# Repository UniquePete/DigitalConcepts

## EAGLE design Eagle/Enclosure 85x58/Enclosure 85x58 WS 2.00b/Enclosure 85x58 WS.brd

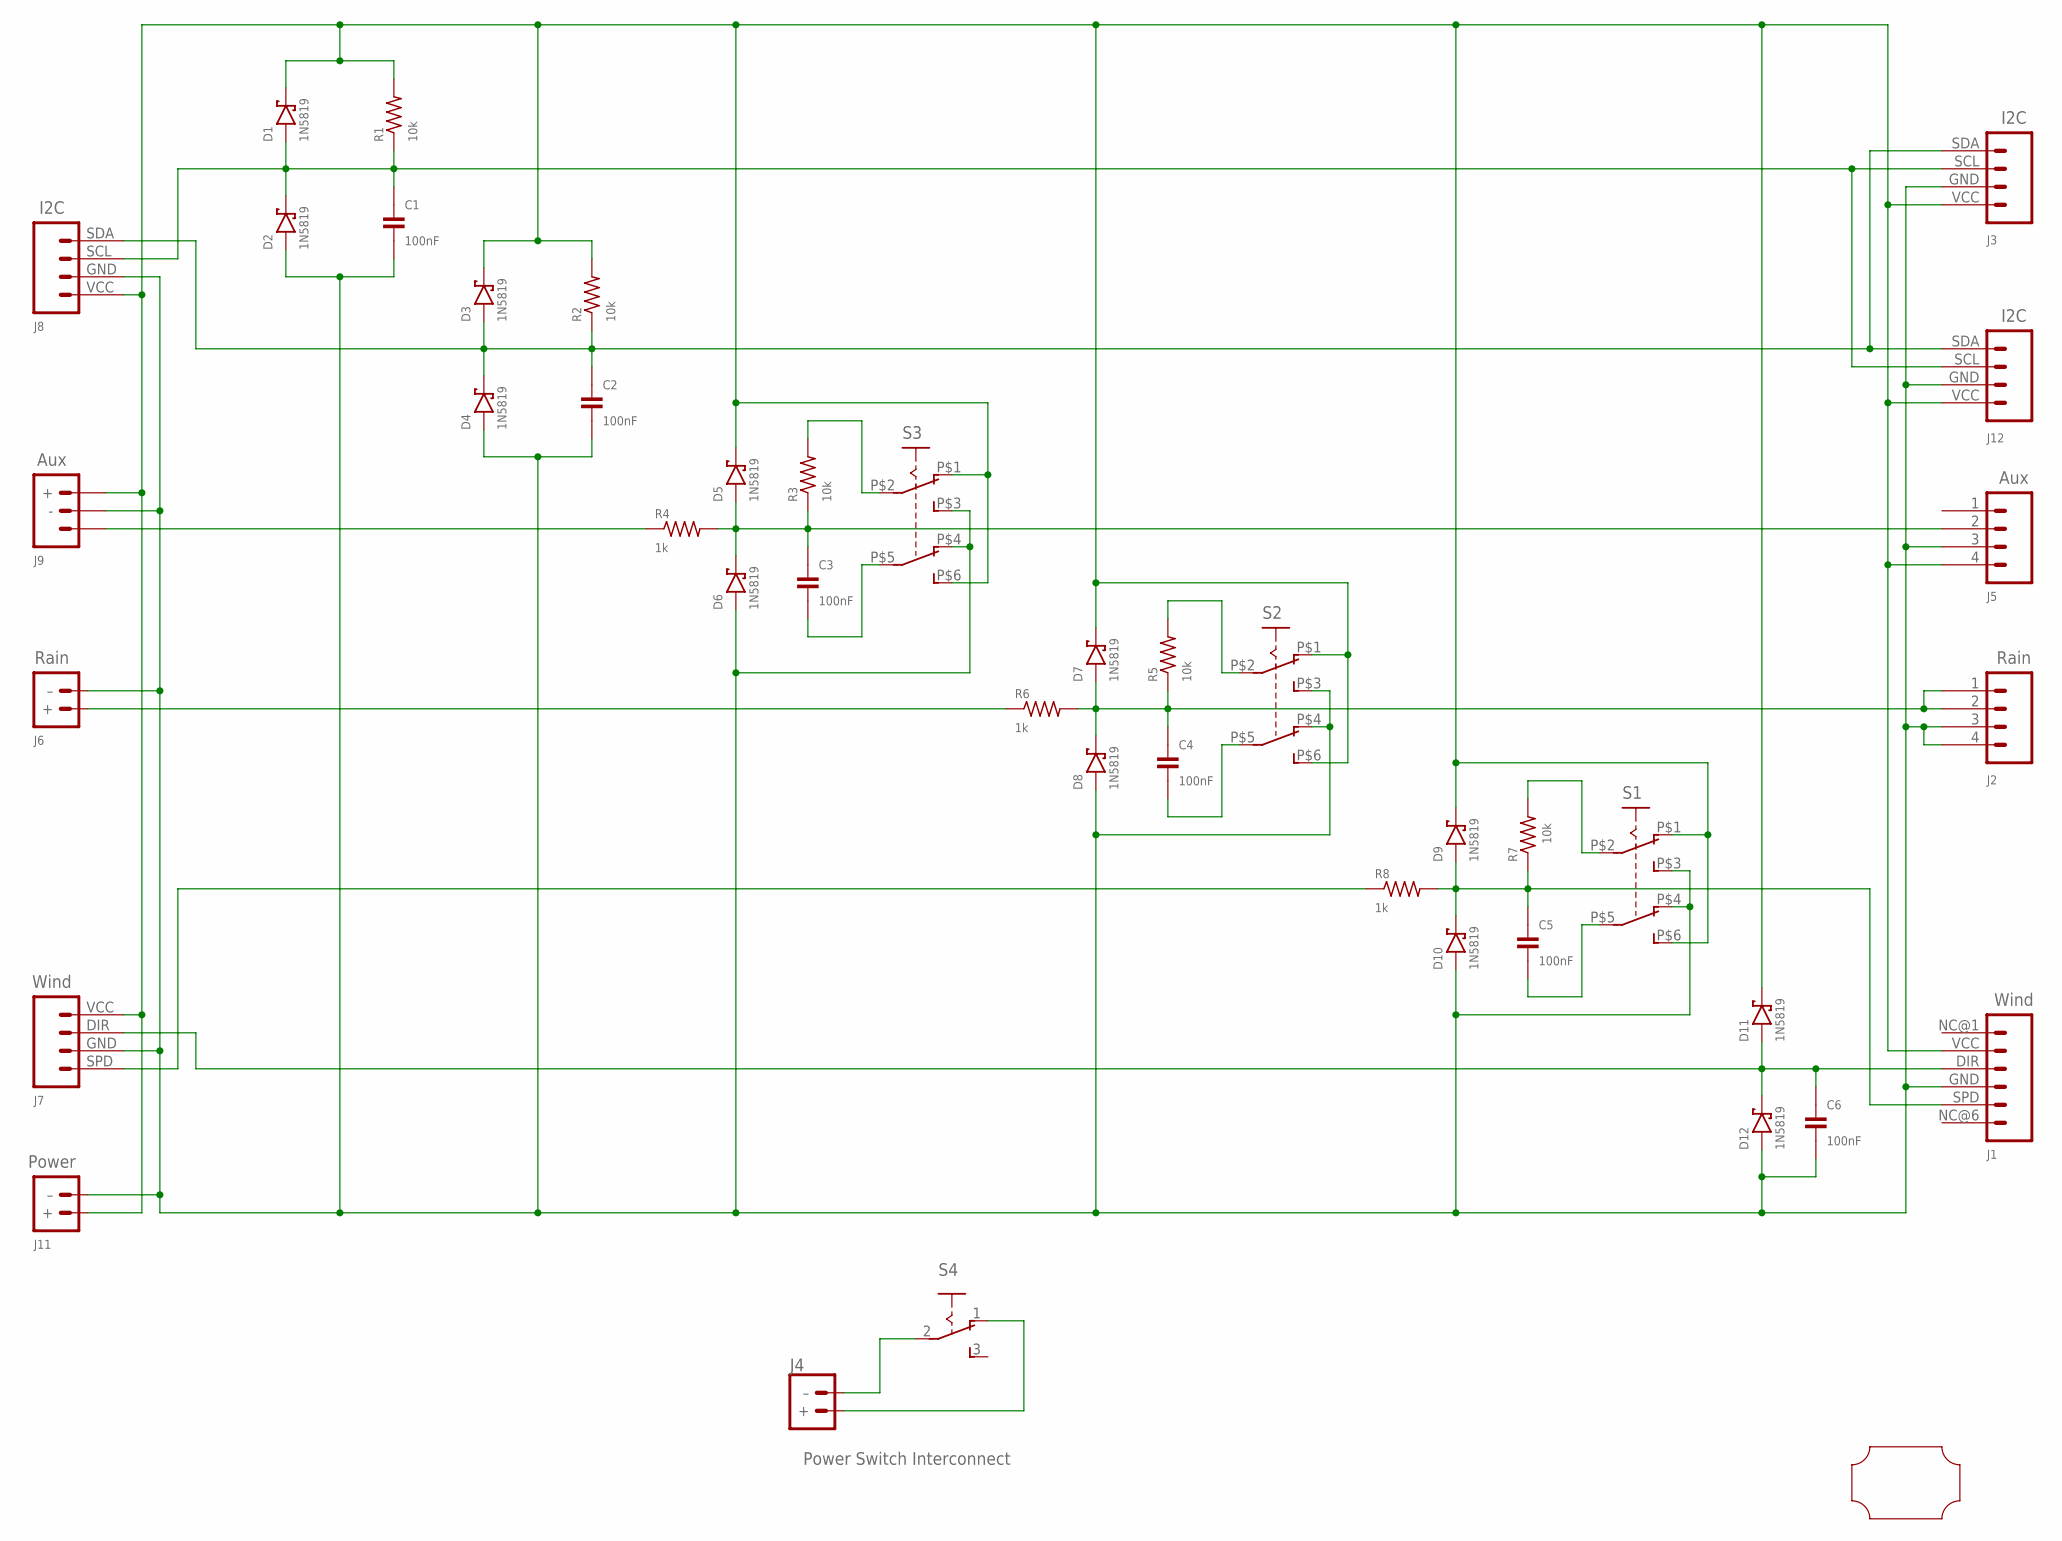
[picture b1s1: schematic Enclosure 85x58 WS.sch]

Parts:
C1, C2, C6: 100nF; C0805-VIA-2
C3, C4, C5: 100nF; C0805
D1, D3, D5, D7, D9, D11: 1N5819; SOD-123
D2, D4, D6, D8, D10, D12: 1N5819; SOD-123-VIA-A
J1: Wind; RJ11-6-VERTICAL-WIND
J2: Rain; RJ11-4-VERTICAL
J3: I2C; RJ11-4-VERTICAL-I2C
J4: JST-PH2.0-2-HORIZONTALJST-PTH-2; JST-PH2.0-2-HORIZONTAL
J5: Aux; RJ11-4-VERTICAL
J6: Rain; JST-PH2.0-2-DUAL-POWER
J7: Wind; JST-PH2.0-4-DUAL-WIND
J8: I2C; JST-PH2.0-4-DUAL-I2C
J9: Aux; JST-PH2.0-3-DUAL
J11: Power; JST-PH2.0-2-DUAL-POWER
J12: I2C; CONN_04-I2C
R1, R2: 10k; R0805-VIA-1
R3, R5, R7: 10k; R0805
R4, R6, R8: 1k; R0805-VIA-1
S1, S2, S3: SWITCH-SLIDE-DPDT; SWITCH-DPDT-SMD
S4: SWITCH-SLIDE-SPDT; SWITCH-SPDT-PTH
U$1: PCB-OUTLINE-85X58; PROTO-28X18-OUTLINE

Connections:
GND: C1.2, C1.2@VIA (2), C2.2, C2.2@VIA (2), C6.2, C6.2@VIA (2), D2.A, D2.P$A (A), D4.A, D4.P$A (A), D6.A, D6.P$A (A), D8.A, D8.P$A (A), D10.A, D10.P$A (A), D12.A, D12.P$A (A), J1.GND (4), J2.3 (2), J2.4 (1), J3.GND (2), J5.3 (2), J6.- (–), J7.GND (3), J8.GND (3), J9.-, J11.- (–), J12.GND (2), S1.P$3 (S1), S1.P$4 (O2), S2.P$3 (S1), S2.P$4 (O2), S3.P$3 (S1), S3.P$4 (O2)
unnamed: J6.+, R6.1, R6.1@VIA (1)
unnamed: C5.2, S1.P$5 (P2)
unnamed: R7.2, S1.P$2 (P1)
unnamed: C6.1, D11.A, D12.C, J1.DIR (3), J7.DIR (2)
unnamed: R5.2, S2.P$2 (P1)
unnamed: C4.2, S2.P$5 (P2)
unnamed: C4.1, D7.A, D8.C, J2.1 (4), J2.2 (3), R5.1, R6.2
unnamed: C2.1, D3.A, D4.C, J3.SDA (4), J8.SDA (1), J12.SDA (4), R2.1, R2.1@VIA (1)
unnamed: J9.SIG, R4.1, R4.1@VIA (1)
unnamed: J7.SPD (4), R8.1, R8.1@VIA (1)
unnamed: C1.1, D1.A, D2.C, J3.SCL (3), J8.SCL (2), J12.SCL (3), R1.1, R1.1@VIA (1)
unnamed: R3.2, S3.P$2 (P1)
unnamed: C3.2, S3.P$5 (P2)
unnamed: J4.2 (–), S4.2
unnamed: C3.1, D5.A, D6.C, J5.2 (3), R3.1, R4.2
unnamed: J4.1 (+), S4.1 (O)
unnamed: C5.1, D9.A, D10.C, J1.SPD (5), R7.1, R8.2
VCC: D1.C, D3.C, D5.C, D7.C, D9.C, D11.C, J1.VCC (2), J3.VCC (1), J5.4 (1), J7.VCC (1), J8.VCC (4), J9.+, J11.+, J12.VCC (1), R1.2, R2.2, S1.P$1 (O1), S1.P$6 (S2), S2.P$1 (O1), S2.P$6 (S2), S3.P$1 (O1), S3.P$6 (S2)

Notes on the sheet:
Power Switch Interconnect

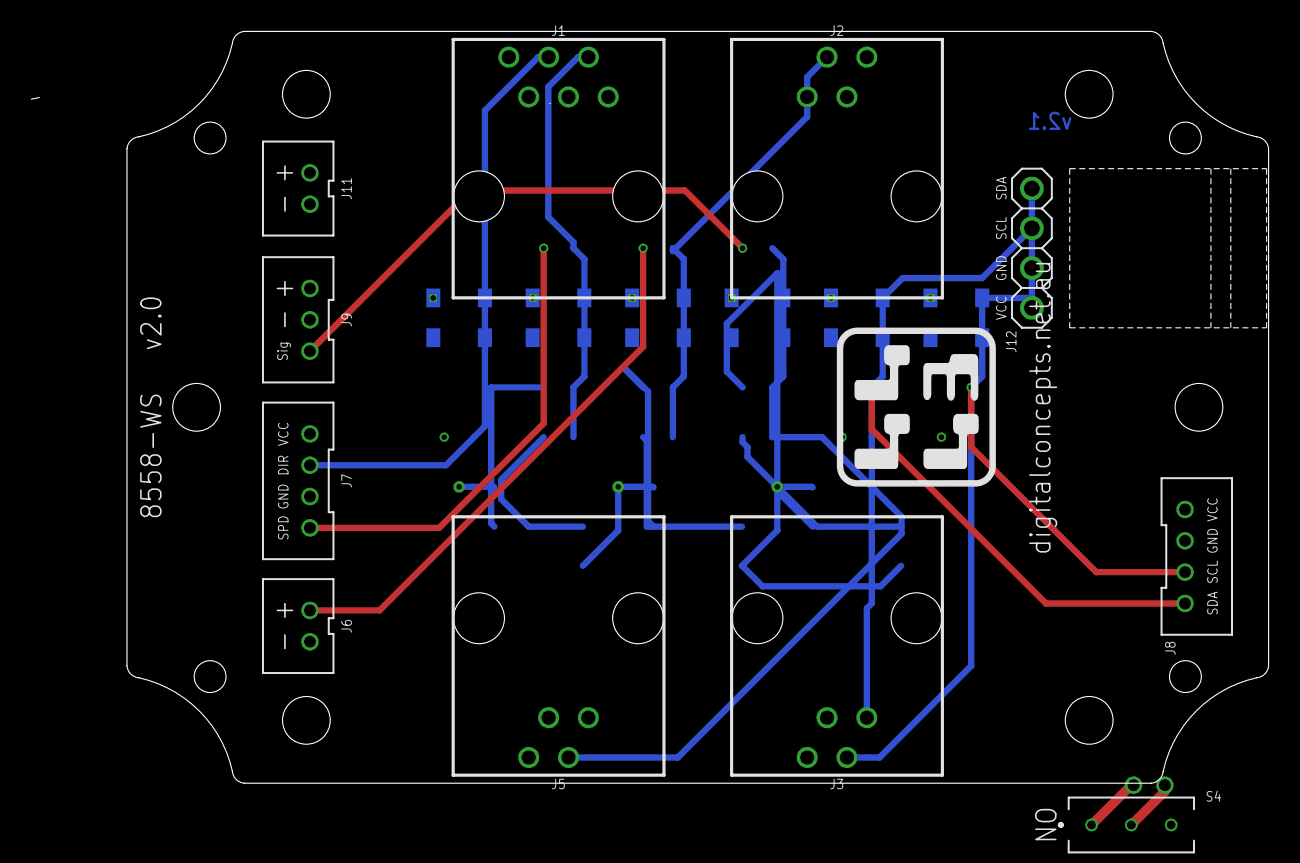
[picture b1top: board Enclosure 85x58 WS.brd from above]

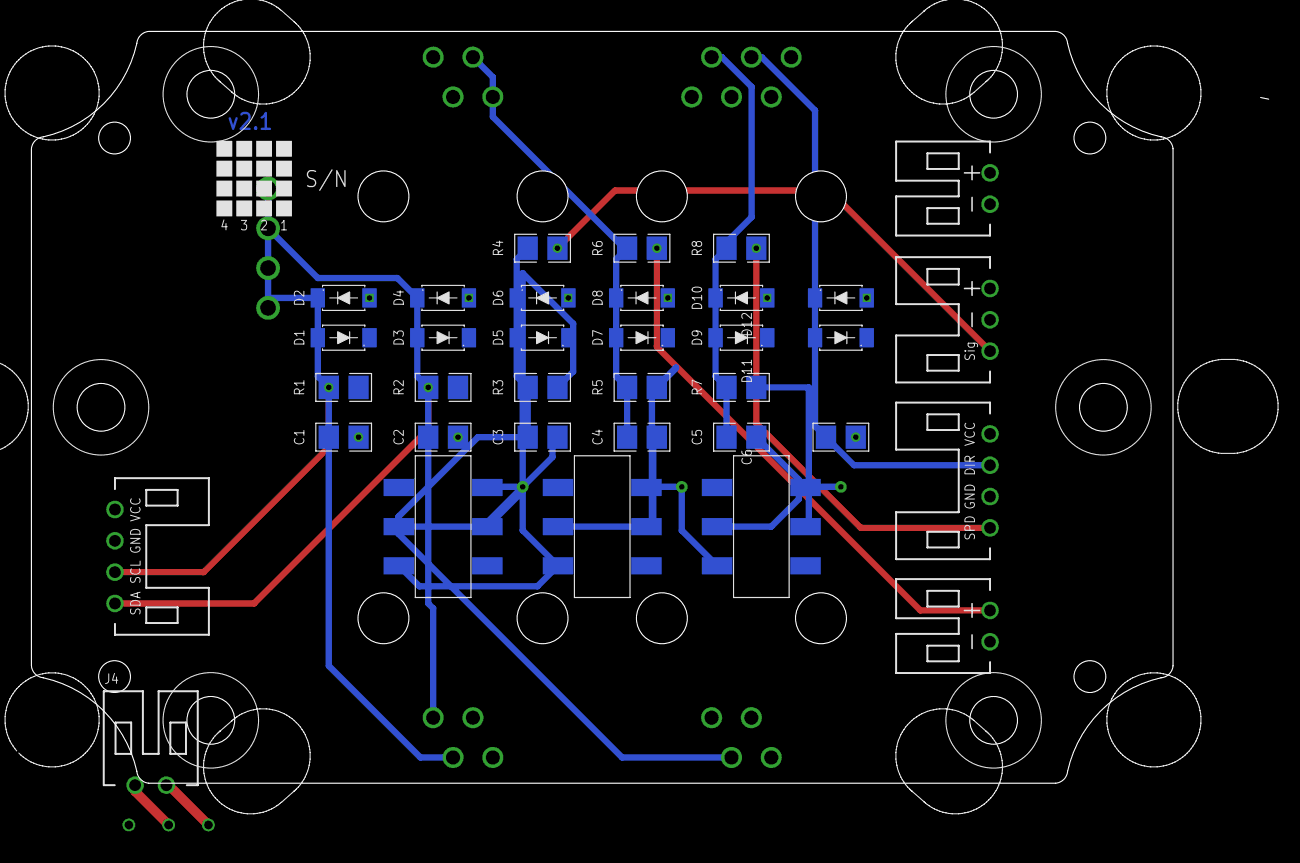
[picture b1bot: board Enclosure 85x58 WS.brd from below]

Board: 2 copper layers, 79.0 x 48.0 mm, 42 parts (35 on the bottom side), 19 nets.

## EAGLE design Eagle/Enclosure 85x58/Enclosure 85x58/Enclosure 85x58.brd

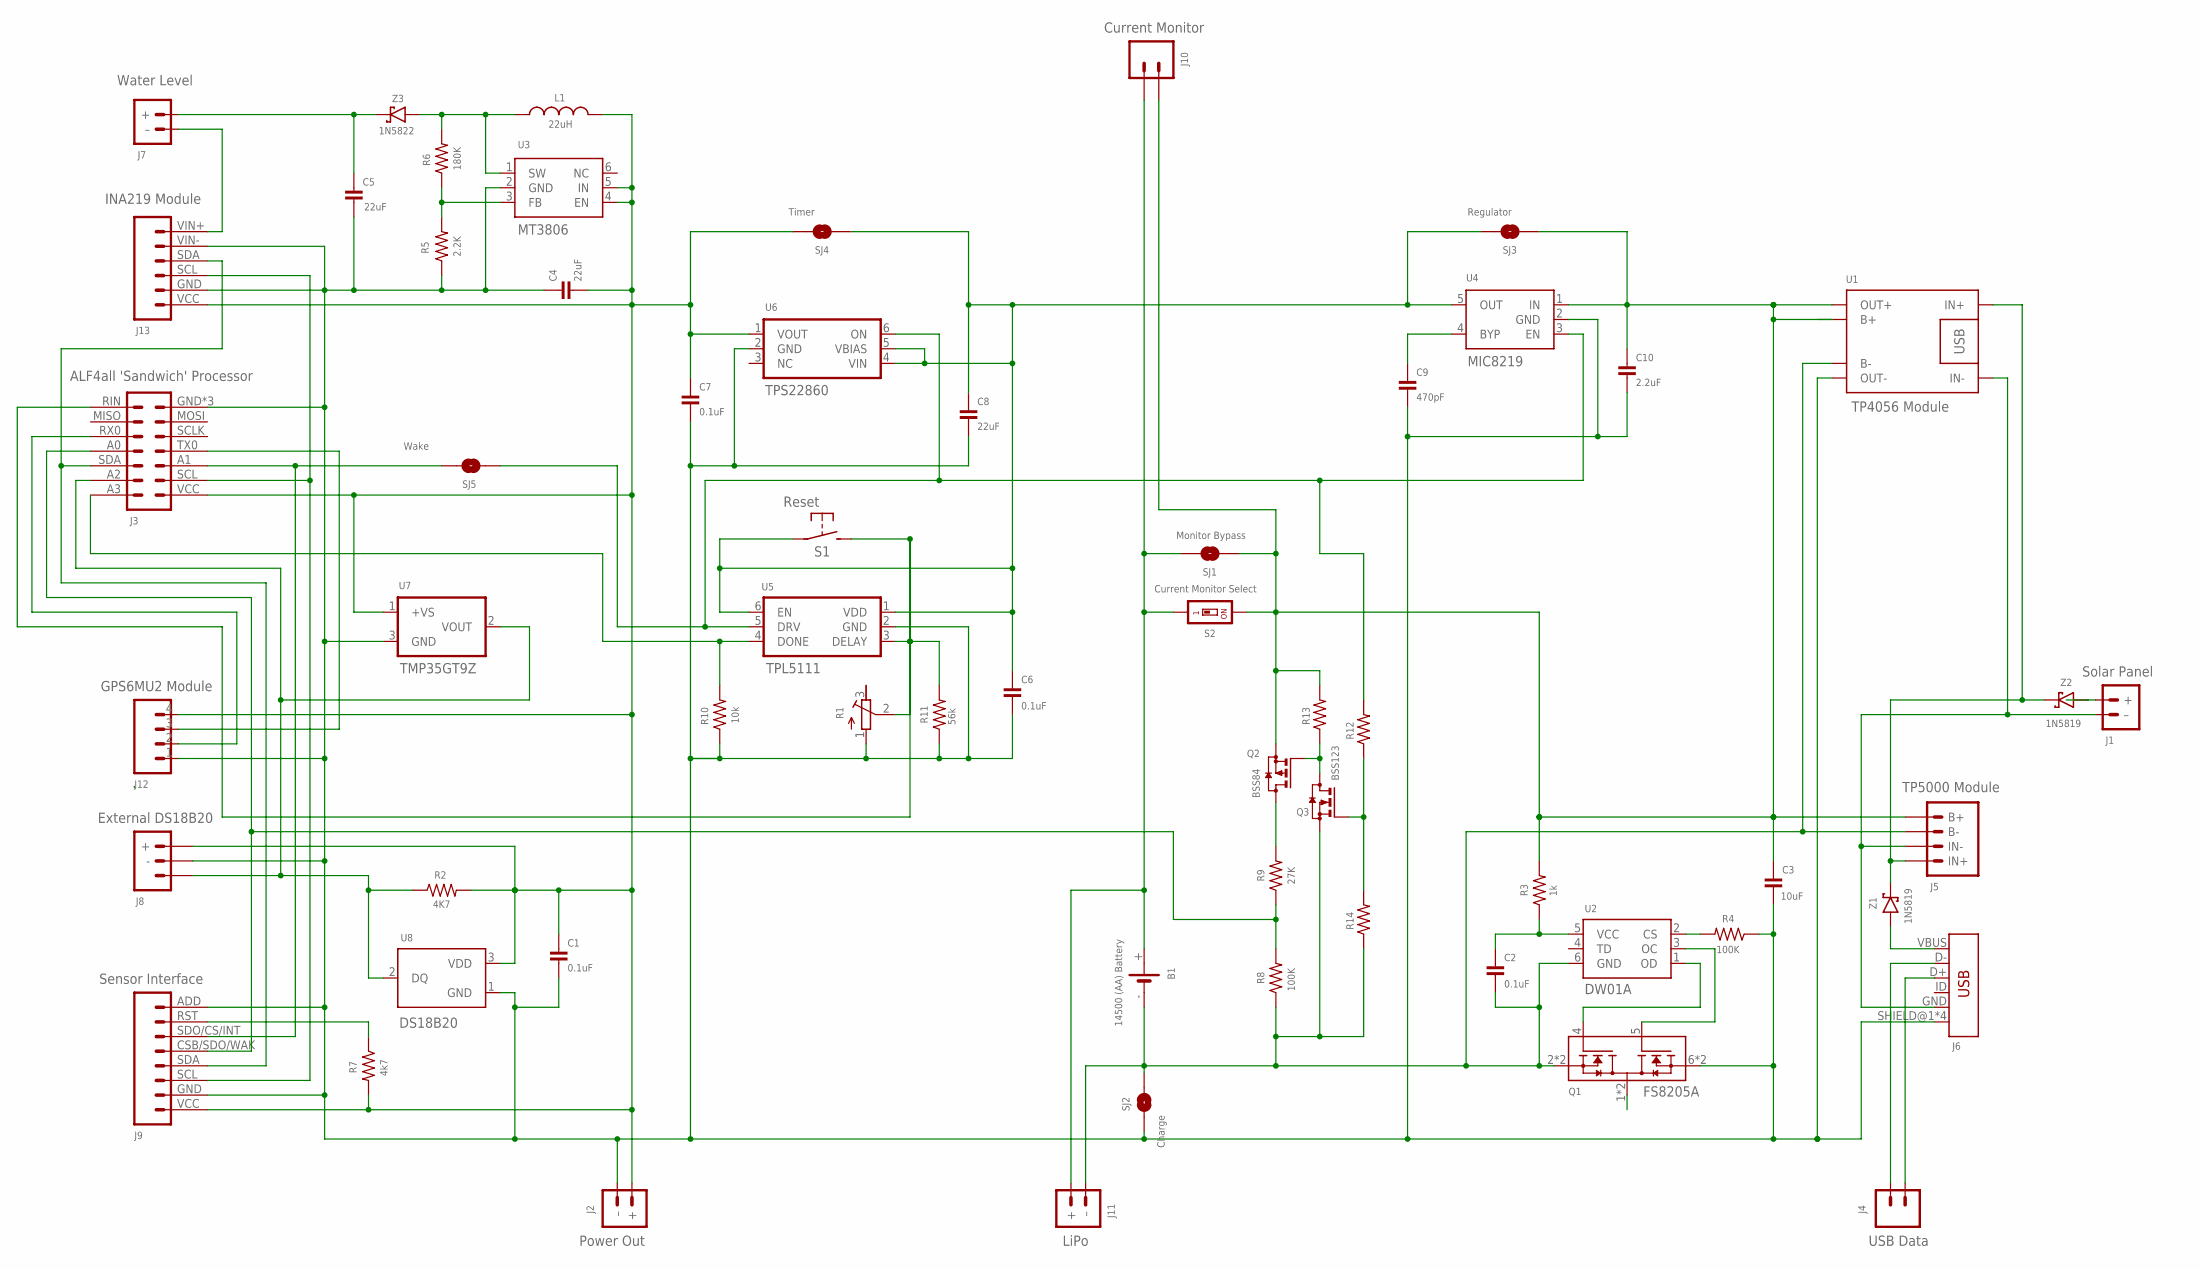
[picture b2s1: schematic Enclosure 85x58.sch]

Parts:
B1: 14500 (AA) Battery; BATTERY-14500
C1: 0.1uF; C0805-VIA-2
C2, C7: 0.1uF; C0805-VIA-1
C3: 10uF; C0805-VIA-2
C4: 22uF; C0805-VIA-1
C5: 22uF; C0805
C6: 0.1uF; C0805
C8: 22uF; C0805-VIA-2
C9: 470pF; C0805
C10: 2.2uF; C0805-VIA-2
J1: Solar Panel; JST-PH2.0-2-VERTICAL
J2: Power Out; JST-PH1.25-2
J3: ALF4all 'Sandwich' Processor; CONN_2X7-ALF4ALL-PROCESSOR
J4: USB Data; CONN_02-GENERIC
J5: TP5000 Module; CONN_04-GENERIC
J6: USB; USB-MINIB
J7: Water Level; JST-PH2.0-2-VERTICAL
J8: External DS18B20; JST-PH2.0-3-VERTICAL
J9: Sensor Interface; CONN_08-SENSOR
J10: Current Monitor; JST-PH2.0-2-HORIZONTAL
J11: LiPo; JST-PH2.0-2-VERTICAL
J12: GPS6MU2 Module; CONN_04-GENERIC
J13: INA219 Module; CONN_06-INA219
L1: 22uH; L5038P
Q1: FS8205A; SOP65P640X120-8N
Q2: BSS84; SOT23
Q3: BSS123; SOT23
R1: RESISTOR-TRIMM64W; RTRIM64W
R2: 4K7; R0805
R3: 1k; R0805
R4, R8: 100K; R0805
R5: 2.2K; R0805-VIA-1
R6: 180K; R0805
R7: 4k7; R0805
R9: 27K; R0805-VIA-12
R10: 10k; R0805-VIA-2
R11: 56k; R0805-VIA-1
R12, R13, R14: RESISTORR0805; R0805
S1: Reset; SWITCH-2-PAD-VIAS
S2: Current Monitor Select; SMD-001-VIA-1
SJ1: Monitor Bypass; SJ
SJ2: Charge; SJ-VIA-2
SJ3: Regulator; SJ-VIA-1
SJ4: Timer; SJ
SJ5: Wake; SJ-VIA-1
U1: TP4056 Module; BATTERY-CHARGER-LI-PROT
U2: DW01A; SOT23-6
U3: MT3806; SOT-23-6
U4: MIC8219; SOT-23-5
U5: TPL5111; SOT-23-6
U6: TPS22860; SOT-23-6
U7: TMP35GT9Z; TO-92
U8: DS18B20; TO-92
Z1, Z2: 1N5819; SOD-123
Z3: 1N5822; SOD-123

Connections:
GND: C1.2, C1.2@VIA (2), C3.2, C3.2@VIA (2), C4.1, C4.1@VIA (1), C5.2, C6.1, C7.1, C7.1@VIA (1), C8.2, C8.2@VIA (2), C9.2, C10.1, J2.- (–), J3.GND (7), J3.GND@TL (7), J3.GND@TR (7), J6.SHIELD@1 (SHIELD), J6.SHIELD@2 (SHIELD), J6.SHIELD@3 (SHIELD), J6.SHIELD@4 (SHIELD), J8.-, J9.ADD (8), J9.GND (2), J12.1, J13.GND (2), J13.VIN- (5), Q1.6 (S2), Q1.7 (S2), R1.1 (A), R4.1, R5.1, R5.1@VIA (1), R10.1, R11.1, R11.1@VIA (1), SJ2.1, SJ2.1@V (1), U1.OUT-, U3.2 (GND), U4.2 (GND), U5.2 (GND), U6.2 (GND), U7.3 (GND), U8.1 (GND)
unnamed: J1.+, Z2.A
unnamed: J1.- (–), J5.2 (IN-), J6.GND, U1.IN-
unnamed: R4.2, U2.2 (CS)
unnamed: Q1.1 (D12), Q1.8 (D12)
unnamed: J5.1 (IN+), U1.IN+, Z1.C, Z2.C
unnamed: L1.1, R6.2, U3.1 (SW), Z3.A
unnamed: C9.1, U4.4 (BYP)
unnamed: J3.SCL (2), J9.SCL (3), J13.SCL (3)
unnamed: J9.RST (7), R7.1
unnamed: J3.A0 (11), J9.CSB/SDO/WAK (5), R8.2, R9.1, R9.1@VIA (1)
unnamed: J3.SDA (12), J9.SDA (4), J13.SDA (4)
unnamed: B1.+, J10.+ (2), J11.+, S2.1, S2.1@VIA (1), SJ1.1
unnamed: J3.A2 (13), J8.SIG, R2.1, U7.2 (VOUT), U8.2 (DQ)
unnamed: J3.TX0 (4), J12.3
unnamed: J7.- (–), J13.VIN+ (6)
unnamed: J3.RX0 (10), J12.2
unnamed: Q1.5 (G2), U2.3 (OC)
unnamed: J6.VBUS, Z1.A
unnamed: Q1.4 (G1), U2.1 (OD)
unnamed: J4.2, J6.D+
unnamed: C2.1, C2.1@VIA (1), R3.1, U2.5 (VCC)
unnamed: Q2.3 (D), R9.2, R9.2@VIA (2)
unnamed: J4.1, J6.D-
unnamed: J3.RIN (8), R1.2 (S), R11.2, S1.2 (S), S1.2@VIA (S), U5.3 (DELAY)
unnamed: C6.2, C8.1, S1.1, S1.1@VIA, SJ3.2, SJ4.2, U4.5 (OUT), U5.1 (VDD), U5.6 (EN), U6.4 (VIN), U6.5 (VBIAS)
unnamed: R12.2, SJ5.2, U4.3 (EN), U5.5 (DRV), U6.6 (ON)
unnamed: J3.A3 (14), R10.2, R10.2@VIA (2), U5.4 (DONE)
unnamed: J3.A1 (3), J9.SDO/CS/INT (6), SJ5.1, SJ5.1@V (1)
unnamed: C5.1, J7.+, Z3.C
unnamed: R5.2, R6.1, U3.3 (FB)
unnamed: C3.1, C10.2, C10.2@VIA (2), J5.4 (B+), J10.- (1), Q2.2 (S), R3.2, R13.2, S2.2, SJ1.2, SJ3.1, SJ3.1@V (1), U1.B+, U1.OUT+, U4.1 (IN)
unnamed: Q2.1 (G), Q3.3 (D), R13.1
unnamed: Q3.1 (G), R12.1, R14.2
unnamed: B1.-, C2.2, J5.3 (B-), J11.- (–), Q1.2 (S1), Q1.3 (S1), Q3.2 (S), R8.1, R14.1, SJ2.2, SJ2.2@V (2), U1.B-, U2.6 (GND)
VCC: C1.1, C4.2, C7.2, J2.+, J3.VCC (1), J8.+, J9.VCC (1), J12.4, J13.VCC (1), L1.2, R2.2, R7.2, SJ4.1, U3.4 (EN), U3.5 (IN), U6.1 (VOUT), U7.1 (+VS), U8.3 (VDD)

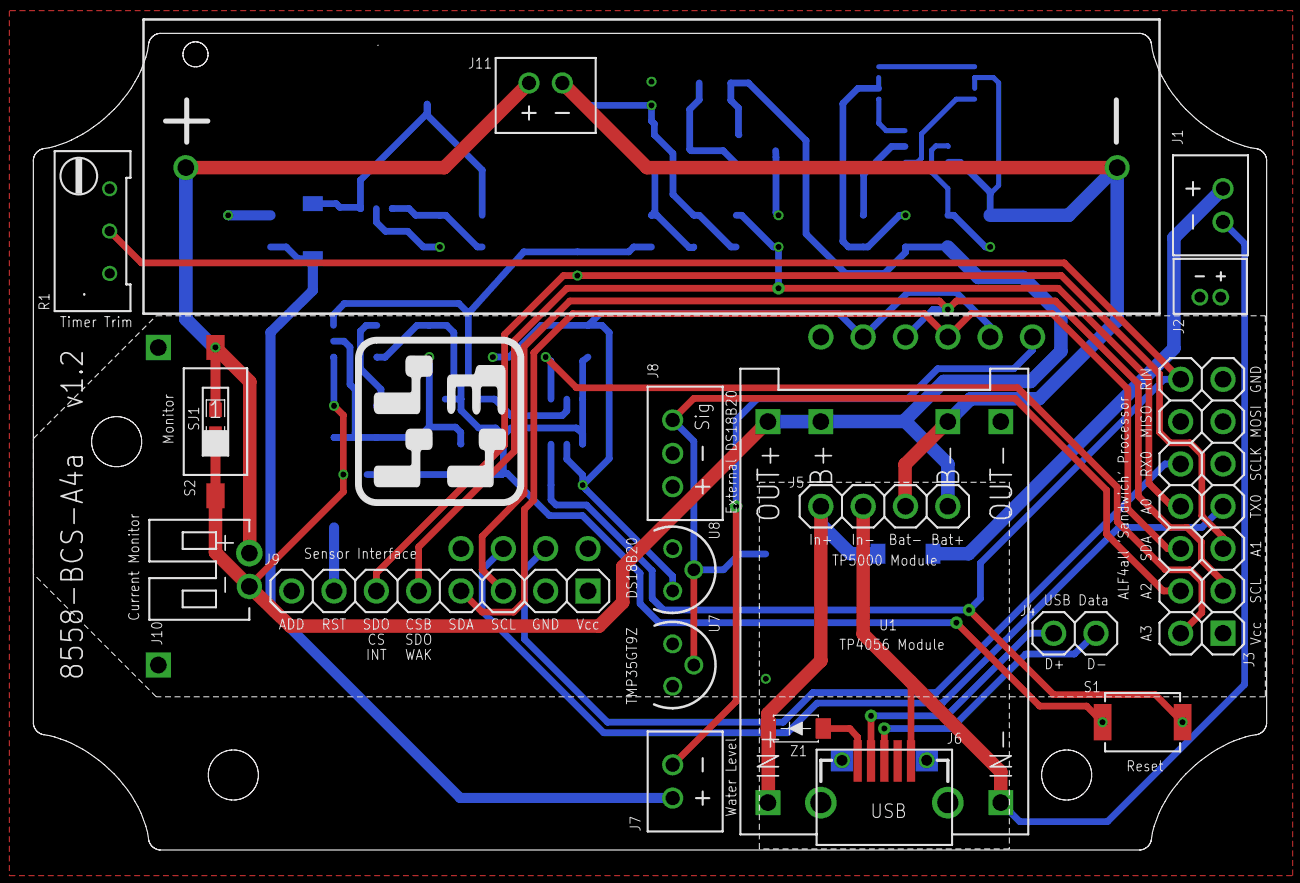
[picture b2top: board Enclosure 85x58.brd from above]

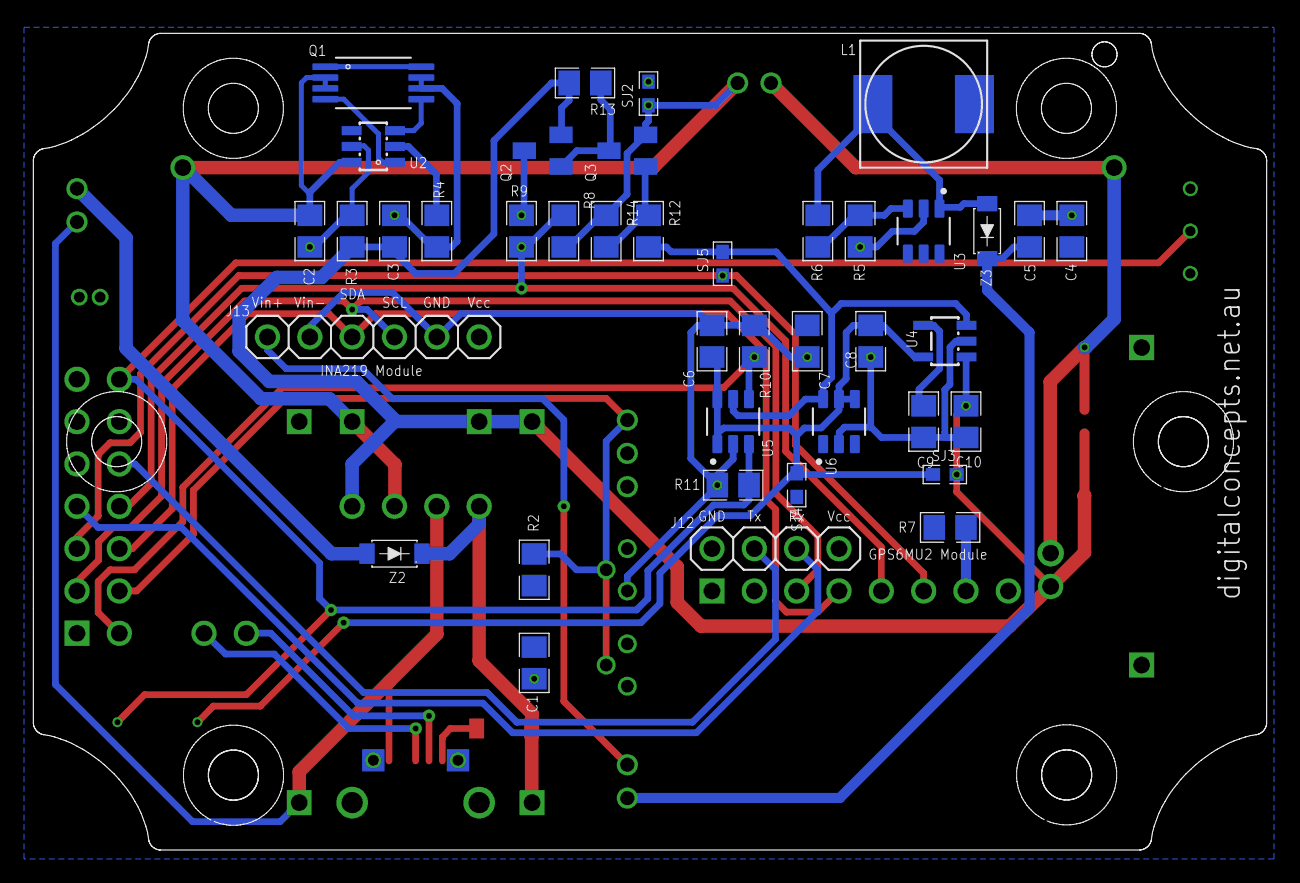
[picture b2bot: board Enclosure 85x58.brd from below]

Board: 2 copper layers, 74.0 x 49.0 mm, 60 parts (40 on the bottom side), 36 nets.

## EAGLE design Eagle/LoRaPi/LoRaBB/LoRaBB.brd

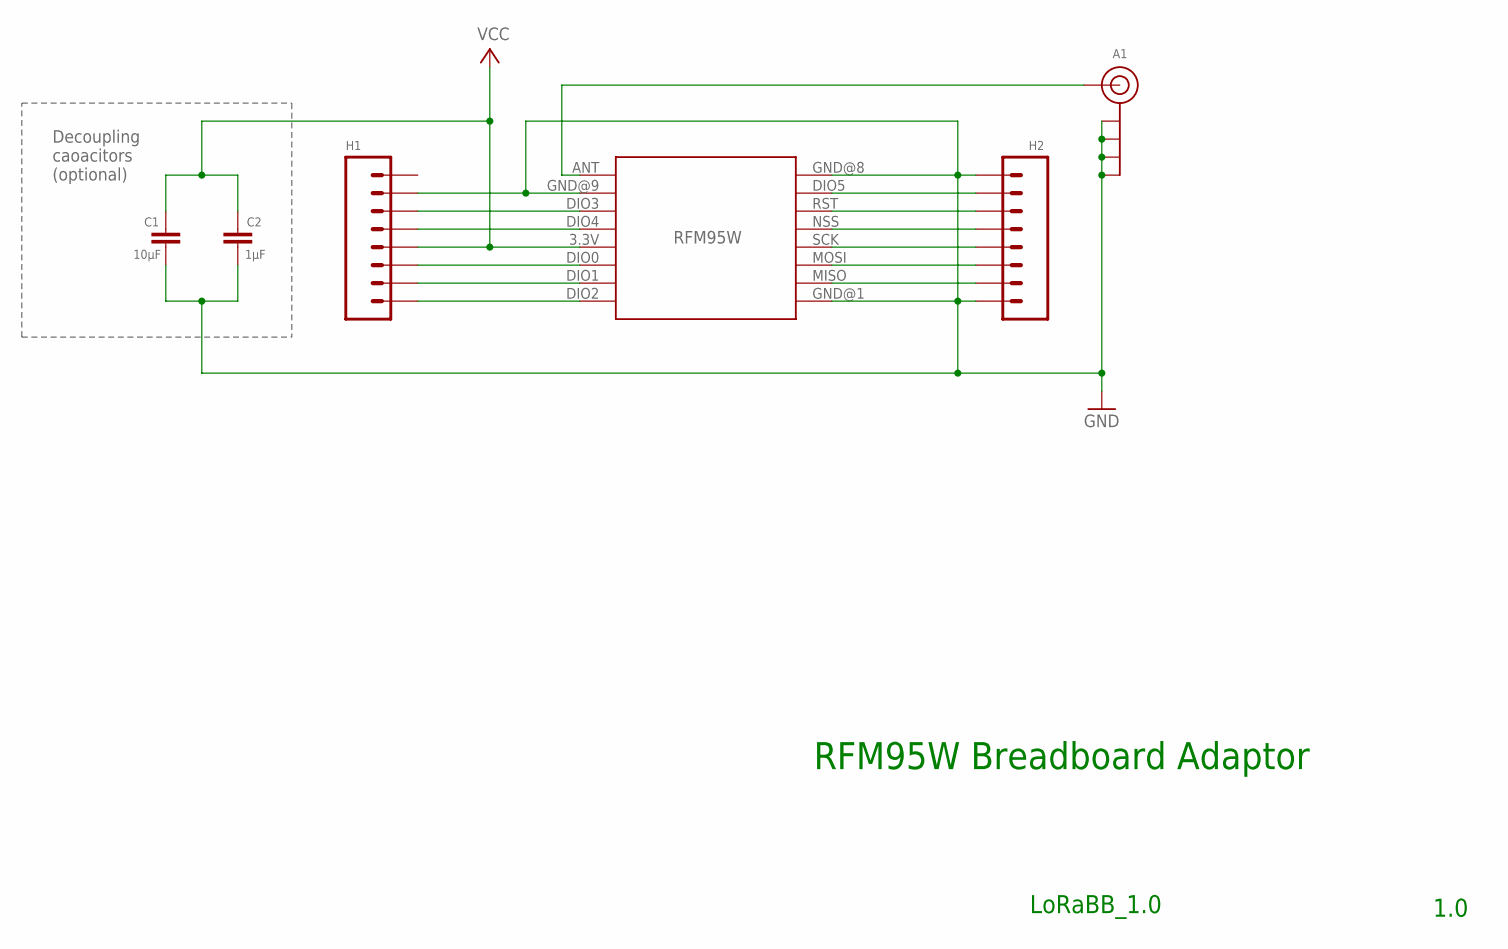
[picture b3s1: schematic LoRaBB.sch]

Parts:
A1: U.FL-SMA-EDGE-COMBO
C1: 10µF; C0805
C2: 1µF; C0805
H1, H2: 1X8-PIN-HEADER; 1X8
RFM95W: RFM95W-LORA

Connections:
GND: A1.GND@1A (GND), A1.GND@1B (GND), A1.GND@2A (GND), A1.GND@2B (GND), C1.2, C2.2, H1.2, H2.1, H2.8, RFM95W.GND@1 (GND.1), RFM95W.GND@8 (GND.2), RFM95W.GND@9 (GND.3)
unnamed: H2.2, RFM95W.DIO5
unnamed: H2.4, RFM95W.NSS
unnamed: H1.4, RFM95W.DIO4
unnamed: H1.3, RFM95W.DIO3
unnamed: A1.SIG, RFM95W.ANT
unnamed: H1.7, RFM95W.DIO1
unnamed: H2.3, RFM95W.RST
unnamed: H2.5, RFM95W.SCK
unnamed: H2.6, RFM95W.MOSI
unnamed: H2.7, RFM95W.MISO
unnamed: H1.6, RFM95W.DIO0
unnamed: H1.8, RFM95W.DIO2
VCC: C1.1, C2.1, H1.5, RFM95W.3.3V

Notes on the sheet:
1.0
Decoupling caoacitors (optional)
RFM95W Breadboard Adaptor
LoRaBB_1.0

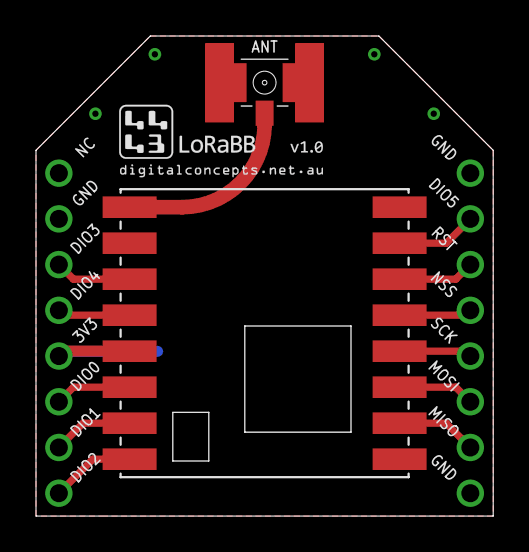
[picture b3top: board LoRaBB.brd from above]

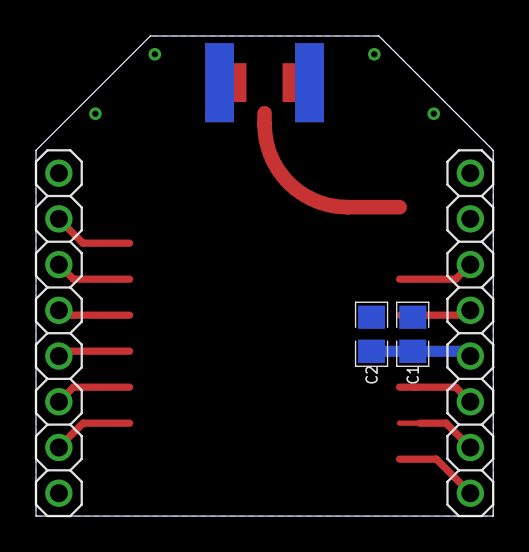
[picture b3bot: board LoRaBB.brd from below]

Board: 2 copper layers, 25.4 x 26.7 mm, 6 parts (2 on the bottom side), 14 nets.

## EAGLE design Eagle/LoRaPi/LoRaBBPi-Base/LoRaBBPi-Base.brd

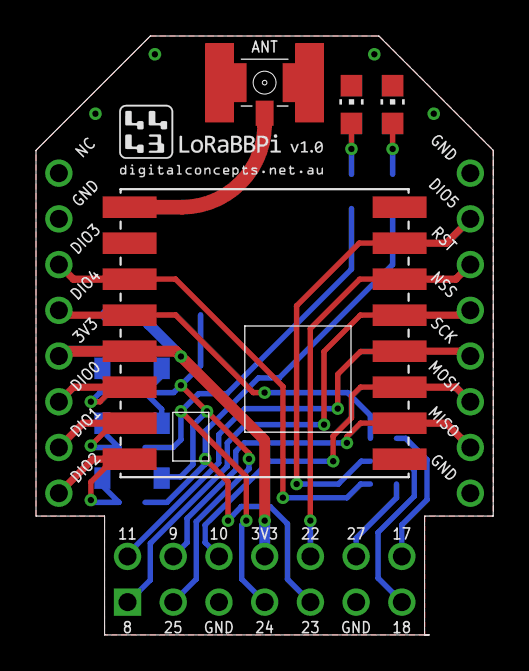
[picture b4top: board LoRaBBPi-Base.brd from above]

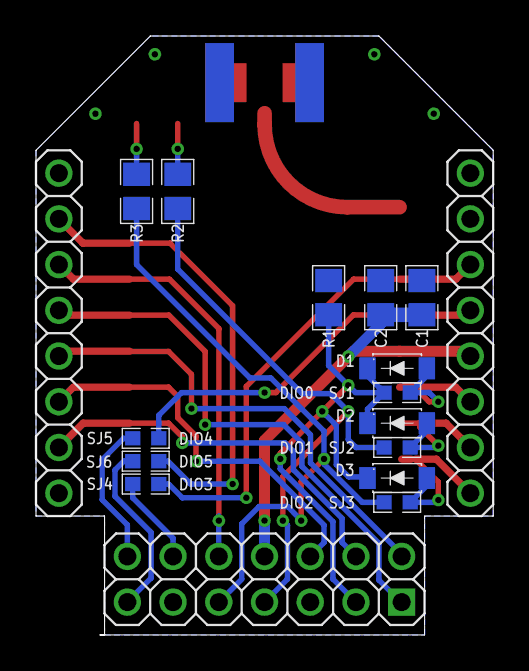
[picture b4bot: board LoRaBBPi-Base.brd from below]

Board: 2 copper layers, 25.4 x 33.3 mm, 21 parts (14 on the bottom side), 22 nets.

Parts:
A1: U.FL-SMA-EDGE-COMBO
C1: 10µF; C0805
C2: 1µF; C0805
D1, D2, D3: 1N4148; SOD-123
H1, H2: 1X8-PIN-HEADER; 1X8
LED1: CS; CHIP-LED0805
LED2: Tx/Rx; CHIP-LED0805
PI: 2X7-PIN-HEADER; 2X7
R1: 10K; R0805
R2, R3: 390; R0805
RFM95W: RFM95W-LORA
SJ1, SJ2, SJ3, SJ4, SJ5, SJ6: SJ

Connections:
GND: A1.GND@1A, A1.GND@1B, A1.GND@2A, A1.GND@2B, C1.2, C2.2, H1.2, H2.1, H2.8, LED1.C, LED2.C, PI.GND@5, PI.GND@11, R1.1, RFM95W.GND@1, RFM95W.GND@8, RFM95W.GND@9
unnamed: LED2.A, R3.1
unnamed: LED1.A, R2.1
unnamed: PI.18, SJ6.1
unnamed: H2.4, PI.8, RFM95W.NSS
unnamed: PI.23, R3.2, SJ3.2
unnamed: PI.24, R2.2, SJ2.2
unnamed: D1.2, H1.6, RFM95W.DIO0, SJ1.1
unnamed: H1.4, RFM95W.DIO4, SJ5.1
unnamed: H1.3, RFM95W.DIO3, SJ4.1
unnamed: D1.1, D2.1, D3.1, PI.25, R1.2, SJ1.2
unnamed: A1.SIG, RFM95W.ANT
unnamed: D2.2, H1.7, RFM95W.DIO1, SJ2.1
unnamed: H2.3, PI.22, RFM95W.RST
unnamed: D3.2, H1.8, RFM95W.DIO2, SJ3.1
unnamed: H2.5, PI.11, RFM95W.SCK
unnamed: H2.6, PI.10, RFM95W.MOSI
unnamed: H2.7, PI.9, RFM95W.MISO
unnamed: PI.27, SJ4.2
unnamed: PI.17, SJ5.2
unnamed: H2.2, RFM95W.DIO5, SJ6.2
VCC: C1.1, C2.1, H1.5, PI.3V3, RFM95W.3.3V
